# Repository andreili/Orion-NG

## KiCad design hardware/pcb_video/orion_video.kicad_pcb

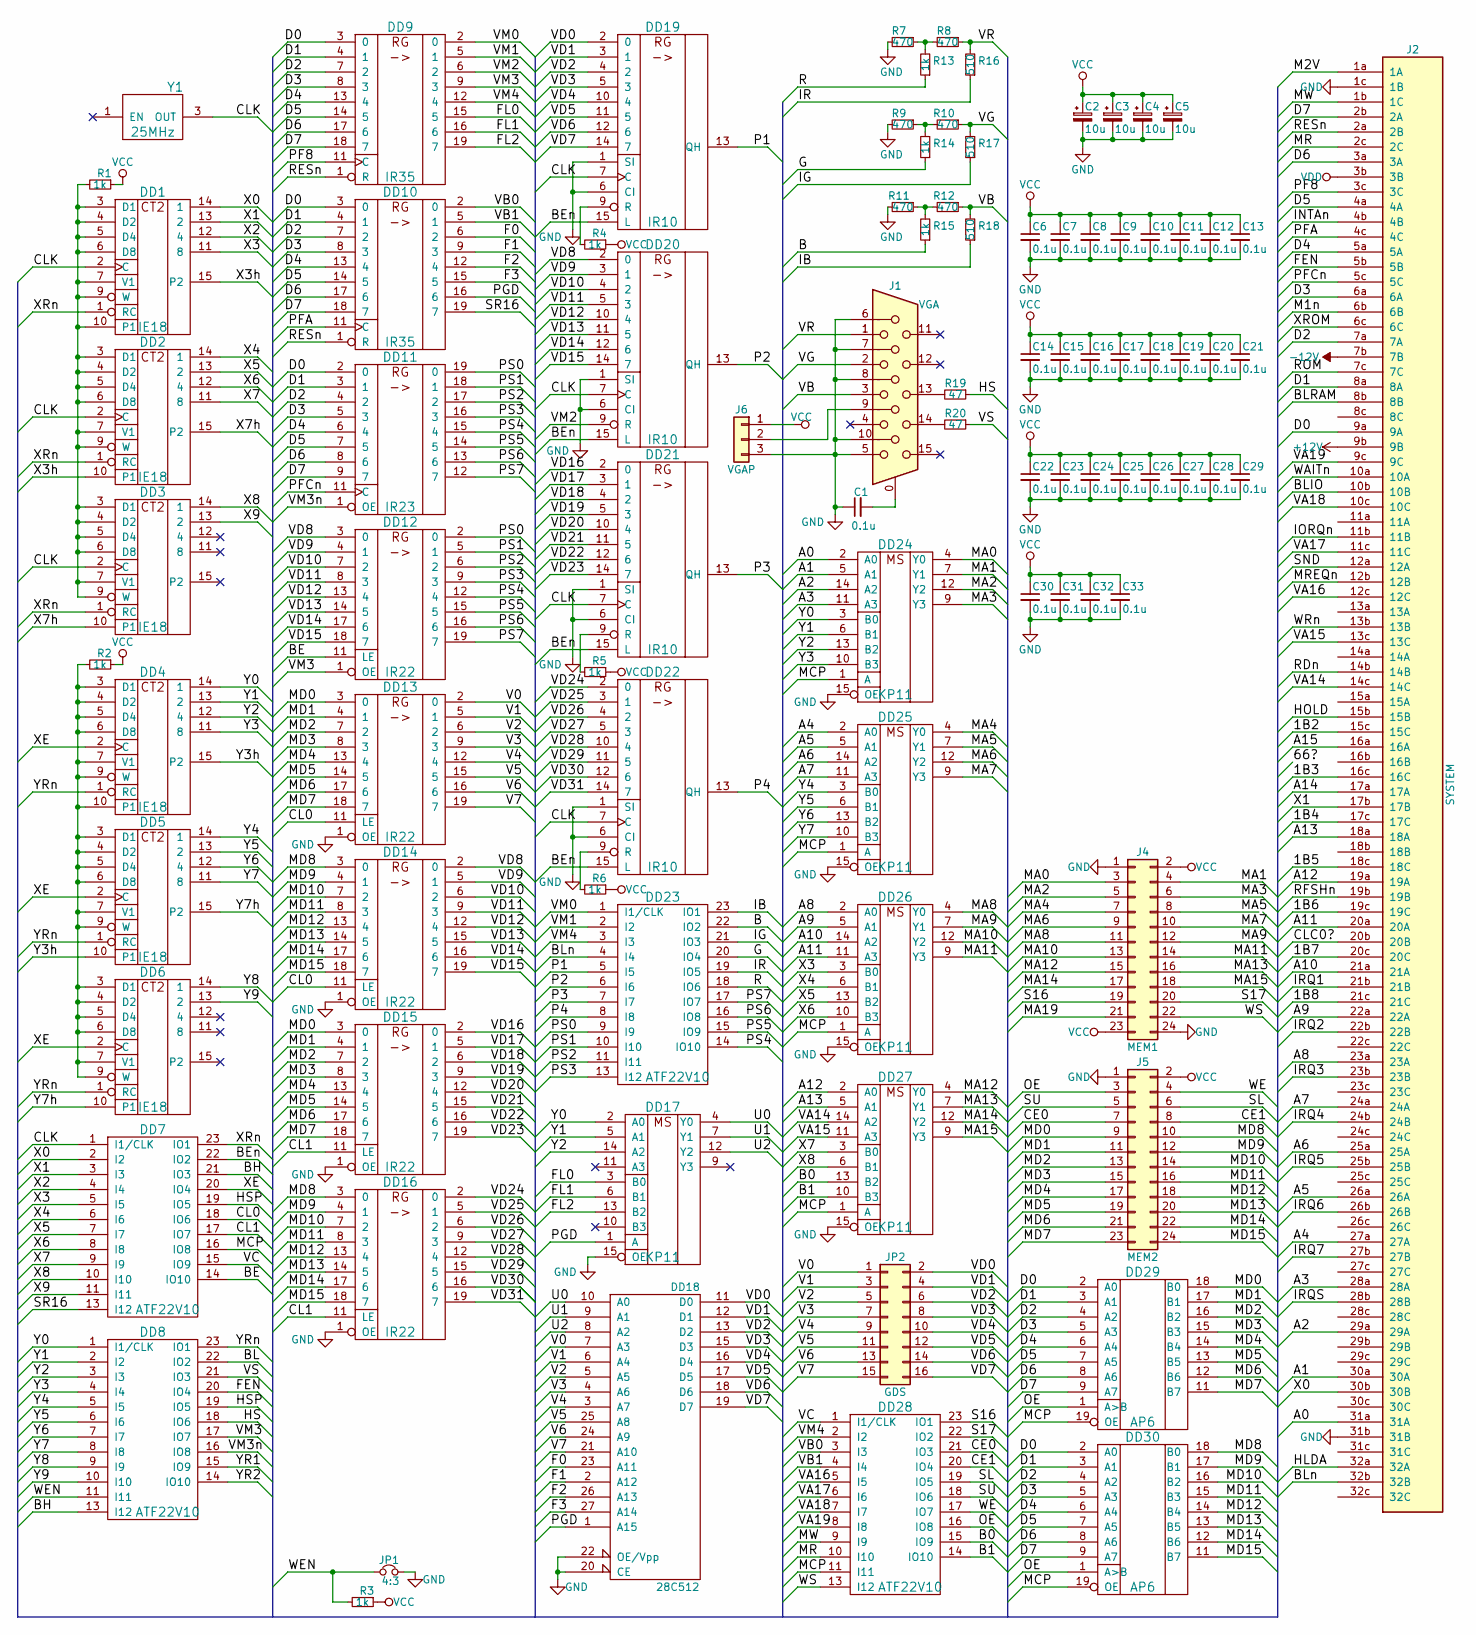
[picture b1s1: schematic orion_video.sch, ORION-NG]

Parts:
C1, C6, C7, C8, C9, C10, C11, C12, C13, C14, C15, C16, C17, C18, C19, C20, C21, C22, C23, C24, C25, C26, C27, C28, C29, C30, C31, C32, C33: 0.1u; C_0805
C2, C3, C4, C5: 10u; CP_Tantalum_Case-B_EIA-3528-21_Hand
DD1, DD2, DD3, DD4, DD5, DD6: IE18; SOIC-16_3.9x9.9mm_Pitch1.27mm
DD7, DD8, DD23, DD28: ATF22V10; DIP-24_W7.62mm_Socket_LongPads
DD9, DD10: IR35; SOIC-20W_7.5x12.8mm_Pitch1.27mm
DD11: IR23; SOIC-20W_7.5x12.8mm_Pitch1.27mm
DD12, DD13, DD14, DD15, DD16: IR22; SOIC-20W_7.5x12.8mm_Pitch1.27mm
DD17, DD24, DD25, DD26, DD27: KP11; SOIC-16_3.9x9.9mm_Pitch1.27mm
DD18: 28C512; DIP-28_W15.24mm_Socket_LongPads
DD19, DD20, DD21, DD22: IR10; SOIC-16_3.9x9.9mm_Pitch1.27mm
DD29, DD30: AP6; SOIC-20W_7.5x12.8mm_Pitch1.27mm
J1: VGA; DB_15F-VGA
J2: SYSTEM; Socket_DIN41612-CaseC1-full-Male-96Pin-3rows
J4: MEM1; Socket_Strip_Straight_2x12_Pitch2.54mm
J5: MEM2; Socket_Strip_Straight_2x12_Pitch2.54mm
J6: VGAP; Socket_Strip_Straight_1x03_Pitch2.54mm
JP1: 4:3; Socket_Strip_Straight_1x02_Pitch2.54mm
JP2: GDS; Socket_Strip_Straight_2x08_Pitch2.54mm
R1, R2, R3, R4, R5, R6, R13, R14, R15: 1k; R_0805
R7, R8, R9, R10, R11, R12: 470; R_0805
R16, R17, R18: 510; R_0805
R19, R20: 47; R_0805
Y1: 25MHz; Crystal_SMD_7050-4pin_7.0x5.0mm

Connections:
+12V: J2.9b (9B)
-12V: J2.7b (7B)
/1B2: J2.15c (15C)
/1B3: J2.16c (16C)
/1B4: J2.17c (17C)
/1B5: J2.18c (18C)
/1B6: J2.19c (19C)
/1B7: J2.20c (20C)
/1B8: J2.21c (21C)
/A0: DD24.2 (A0), J2.31a (31A)
/A1: DD24.5 (A1), J2.30a (30A)
/A2: DD24.14 (A2), J2.29a (29A)
/A3: DD24.11 (A3), J2.28a (28A)
/A4: DD25.2 (A0), J2.27a (27A)
/A5: DD25.5 (A1), J2.26a (26A)
/A6: DD25.14 (A2), J2.25a (25A)
/A7: DD25.11 (A3), J2.24a (24A)
/A8: DD26.2 (A0), J2.23a (23A)
/A9: DD26.5 (A1), J2.22a (22A)
/A10: DD26.14 (A2), J2.21a (21A)
/A11: DD26.11 (A3), J2.20a (20A)
/A12: DD27.2 (A0), J2.19a (19A)
/A13: DD27.5 (A1), J2.18a (18A)
/A14: J2.17a (17A)
/A15: J2.16a (16A)
/B: DD23.22 (IO2), R15.1
/B0: DD27.13 (B2), DD28.15 (IO9)
/B1: DD27.10 (B3), DD28.14 (IO10)
/BE: DD7.14 (IO10), DD12.11 (LE)
/BEn: DD7.22 (IO2), DD19.15 (L), DD20.15 (L), DD21.15 (L), DD22.15 (L)
/BH: DD7.21 (IO3), DD8.13 (I12)
/BL: DD8.22 (IO2)
/BLIO: J2.10b (10B)
/BLRAM: J2.8b (8B)
/BLn: DD23.4 (I4), J2.32b (32B)
/CE0: DD28.21 (IO3), J5.7
/CE1: DD28.20 (IO4), J5.8
/CL0: DD7.18 (IO6), DD13.11 (LE), DD14.11 (LE)
/CL1: DD7.17 (IO7), DD15.11 (LE), DD16.11 (LE)
/CLC0?: J2.20b (20B)
/CLK: DD1.2 (C), DD2.2 (C), DD3.2 (C), DD7.1 (I1/CLK), DD19.7 (C), DD20.7 (C), DD21.7 (C), DD22.7 (C), Y1.3 (OUT)
/D0: DD9.3 (0), DD10.3 (0), DD11.2 (0), DD29.2 (A0), DD30.2 (A0), J2.9a (9A)
/D1: DD9.4 (1), DD10.4 (1), DD11.3 (1), DD29.3 (A1), DD30.3 (A1), J2.8a (8A)
/D2: DD9.7 (2), DD10.7 (2), DD11.4 (2), DD29.4 (A2), DD30.4 (A2), J2.7a (7A)
/D3: DD9.8 (3), DD10.8 (3), DD11.5 (3), DD29.5 (A3), DD30.5 (A3), J2.6a (6A)
/D4: DD9.13 (4), DD10.13 (4), DD11.6 (4), DD29.6 (A4), DD30.6 (A4), J2.5a (5A)
/D5: DD9.14 (5), DD10.14 (5), DD11.7 (5), DD29.7 (A5), DD30.7 (A5), J2.4a (4A)
/D6: DD9.17 (6), DD10.17 (6), DD11.8 (6), DD29.8 (A6), DD30.8 (A6), J2.3a (3A)
/D7: DD9.18 (7), DD10.18 (7), DD11.9 (7), DD29.9 (A7), DD30.9 (A7), J2.2b (2A)
/F0: DD10.6 (2), DD18.23 (A11)
/F1: DD10.9 (3), DD18.2 (A12)
/F2: DD10.12 (4), DD18.26 (A13)
/F3: DD10.15 (5), DD18.27 (A14)
/FEN: DD8.20 (IO4), J2.5b (5B)
/FL0: DD9.15 (5), DD17.3 (B0)
/FL1: DD9.16 (6), DD17.6 (B1)
/FL2: DD9.19 (7), DD17.13 (B2)
/G: DD23.20 (IO4), R14.1
/HLDA: J2.32a (32A)
/HOLD: J2.15b (15B)
/HS: DD8.18 (IO6), R19.1
/HSP: DD7.19 (IO5), DD8.19 (IO5)
/IB: DD23.23 (IO1), R18.1
/IG: DD23.21 (IO3), R17.1
/INTAn: J2.4b (4B)
/IORQn: J2.11b (11B)
/IR: DD23.19 (IO5), R16.1
/IRQ1: J2.21b (21B)
/IRQ2: J2.22b (22B)
/IRQ3: J2.23b (23B)
/IRQ4: J2.24b (24B)
/IRQ5: J2.25b (25B)
/IRQ6: J2.26b (26B)
/IRQ7: J2.27b (27B)
/IRQS: J2.28b (28B)
/M1n: J2.6b (6B)
/M2V: J2.1a (1A)
/MA0: DD24.4 (Y0), J4.3
/MA1: DD24.7 (Y1), J4.4
/MA2: DD24.12 (Y2), J4.5
/MA3: DD24.9 (Y3), J4.6
/MA4: DD25.4 (Y0), J4.7
/MA5: DD25.7 (Y1), J4.8
/MA6: DD25.12 (Y2), J4.9
/MA7: DD25.9 (Y3), J4.10
/MA8: DD26.4 (Y0), J4.11
/MA9: DD26.7 (Y1), J4.12
/MA10: DD26.12 (Y2), J4.13
/MA11: DD26.9 (Y3), J4.14
/MA12: DD27.4 (Y0), J4.15
/MA13: DD27.7 (Y1), J4.16
/MA14: DD27.12 (Y2), J4.17
/MA15: DD27.9 (Y3), J4.18
/MA19: J4.21
/MCP: DD7.16 (IO8), DD24.1 (A), DD25.1 (A), DD26.1 (A), DD27.1 (A), DD28.11 (I11), DD29.19 (OE), DD30.19 (OE)
/MD0: DD13.3 (0), DD15.3 (0), DD29.18 (B0), J5.9
/MD1: DD13.4 (1), DD15.4 (1), DD29.17 (B1), J5.11
/MD2: DD13.7 (2), DD15.7 (2), DD29.16 (B2), J5.13
/MD3: DD13.8 (3), DD15.8 (3), DD29.15 (B3), J5.15
/MD4: DD13.13 (4), DD15.13 (4), DD29.14 (B4), J5.17
/MD5: DD13.14 (5), DD15.14 (5), DD29.13 (B5), J5.19
/MD6: DD13.17 (6), DD15.17 (6), DD29.12 (B6), J5.21
/MD7: DD13.18 (7), DD15.18 (7), DD29.11 (B7), J5.23
/MD8: DD14.3 (0), DD16.3 (0), DD30.18 (B0), J5.10
/MD9: DD14.4 (1), DD16.4 (1), DD30.17 (B1), J5.12
/MD10: DD14.7 (2), DD16.7 (2), DD30.16 (B2), J5.14
/MD11: DD14.8 (3), DD16.8 (3), DD30.15 (B3), J5.16
/MD12: DD14.13 (4), DD16.13 (4), DD30.14 (B4), J5.18
/MD13: DD14.14 (5), DD16.14 (5), DD30.13 (B5), J5.20
/MD14: DD14.17 (6), DD16.17 (6), DD30.12 (B6), J5.22
/MD15: DD14.18 (7), DD16.18 (7), DD30.11 (B7), J5.24
/MR: DD28.10 (I10), J2.2c (2C)
/MREQn: J2.12b (12B)
/MW: DD28.9 (I9), J2.1b (1C)
/OE: DD28.16 (IO8), DD29.1 (A>B), DD30.1 (A>B), J5.3
/P1: DD19.13 (QH), DD23.5 (I5)
/P2: DD20.13 (QH), DD23.6 (I6)
/P3: DD21.13 (QH), DD23.7 (I7)
/P4: DD22.13 (QH), DD23.8 (I8)
/PF8: DD9.11 (C), J2.3c (3C)
/PFA: DD10.11 (C), J2.4c (4C)
/PFCn: DD11.11 (C), J2.5c (5C)
/PGD: DD10.16 (6), DD17.1 (A), DD18.1 (A15)
/PS0: DD11.19 (0), DD12.2 (0), DD23.9 (I9)
/PS1: DD11.18 (1), DD12.5 (1), DD23.10 (I10)
/PS2: DD11.17 (2), DD12.6 (2), DD23.11 (I11)
/PS3: DD11.16 (3), DD12.9 (3), DD23.13 (I12)
/PS4: DD11.15 (4), DD12.12 (4), DD23.14 (IO10)
/PS5: DD11.14 (5), DD12.15 (5), DD23.15 (IO9)
/PS6: DD11.13 (6), DD12.16 (6), DD23.16 (IO8)
/PS7: DD11.12 (7), DD12.19 (7), DD23.17 (IO7)
/R: DD23.18 (IO6), R13.1
/RDn: J2.14b (14B)
/RESn: DD9.1 (R), DD10.1 (R), J2.2a (2B)
/RFSHn: J2.19b (19B)
/ROM: J2.7c (7C)
/S16: DD28.23 (IO1), J4.19
/S17: DD28.22 (IO2), J4.20
/SL: DD28.19 (IO5), J5.6
/SND: J2.12a (12A)
/SR16: DD7.13 (I12), DD10.19 (7)
/SU: DD28.18 (IO6), J5.5
/U0: DD17.4 (Y0), DD18.10 (A0)
/U1: DD17.7 (Y1), DD18.9 (A1)
/U2: DD17.12 (Y2), DD18.8 (A2)
/V0: DD13.2 (0), DD18.7 (A3), JP2.1
/V1: DD13.5 (1), DD18.6 (A4), JP2.3
/V2: DD13.6 (2), DD18.5 (A5), JP2.5
/V3: DD13.9 (3), DD18.4 (A6), JP2.7
/V4: DD13.12 (4), DD18.3 (A7), JP2.9
/V5: DD13.15 (5), DD18.25 (A8), JP2.11
/V6: DD13.16 (6), DD18.24 (A9), JP2.13
/V7: DD13.19 (7), DD18.21 (A10), JP2.15
/VA14: DD27.14 (A2), J2.14c (14C)
/VA15: DD27.11 (A3), J2.13c (13C)
/VA16: DD28.5 (I5), J2.12c (12C)
/VA17: DD28.6 (I6), J2.11c (11C)
/VA18: DD28.7 (I7), J2.10c (10C)
/VA19: DD28.8 (I8), J2.9c (9C)
/VB: J1.3, R12.1, R18.2
/VB0: DD10.2 (0), DD28.3 (I3)
/VB1: DD10.5 (1), DD28.4 (I4)
/VC: DD7.15 (IO9), DD28.1 (I1/CLK)
/VD0: DD18.11 (D0), DD19.2 (0), JP2.2
/VD1: DD18.12 (D1), DD19.3 (1), JP2.4
/VD2: DD18.13 (D2), DD19.4 (2), JP2.6
/VD3: DD18.15 (D3), DD19.5 (3), JP2.8
/VD4: DD18.16 (D4), DD19.10 (4), JP2.10
/VD5: DD18.17 (D5), DD19.11 (5), JP2.12
/VD6: DD18.18 (D6), DD19.12 (6), JP2.14
/VD7: DD18.19 (D7), DD19.14 (7), JP2.16
/VD8: DD12.3 (0), DD14.2 (0), DD20.2 (0)
/VD9: DD12.4 (1), DD14.5 (1), DD20.3 (1)
/VD10: DD12.7 (2), DD14.6 (2), DD20.4 (2)
/VD11: DD12.8 (3), DD14.9 (3), DD20.5 (3)
/VD12: DD12.13 (4), DD14.12 (4), DD20.10 (4)
/VD13: DD12.14 (5), DD14.15 (5), DD20.11 (5)
/VD14: DD12.17 (6), DD14.16 (6), DD20.12 (6)
/VD15: DD12.18 (7), DD14.19 (7), DD20.14 (7)
/VD16: DD15.2 (0), DD21.2 (0)
/VD17: DD15.5 (1), DD21.3 (1)
/VD18: DD15.6 (2), DD21.4 (2)
/VD19: DD15.9 (3), DD21.5 (3)
/VD20: DD15.12 (4), DD21.10 (4)
/VD21: DD15.15 (5), DD21.11 (5)
/VD22: DD15.16 (6), DD21.12 (6)
/VD23: DD15.19 (7), DD21.14 (7)
/VD24: DD16.2 (0), DD22.2 (0)
/VD25: DD16.5 (1), DD22.3 (1)
/VD26: DD16.6 (2), DD22.4 (2)
/VD27: DD16.9 (3), DD22.5 (3)
/VD28: DD16.12 (4), DD22.10 (4)
/VD29: DD16.15 (5), DD22.11 (5)
/VD30: DD16.16 (6), DD22.12 (6)
/VD31: DD16.19 (7), DD22.14 (7)
/VG: J1.2, R10.1, R17.2
/VM0: DD9.2 (0), DD23.1 (I1/CLK)
/VM1: DD9.5 (1), DD23.2 (I2)
/VM2: DD9.6 (2), DD20.9 (R)
/VM3: DD8.17 (IO7), DD9.9 (3), DD12.1 (OE)
/VM3n: DD8.16 (IO8), DD11.1 (OE)
/VM4: DD9.12 (4), DD23.3 (I3), DD28.2 (I2)
/VR: J1.1, R8.1, R16.2
/VS: DD8.21 (IO3), R20.1
/WAITn: J2.10a (10A)
/WE: DD28.17 (IO7), J5.4
/WEN: DD8.11 (I11), JP1.1, R3.2
/WRn: J2.13b (13B)
/WS: DD28.13 (I12), J4.22
/X0: DD1.14 (1), DD7.2 (I2), J2.30b (30B)
/X1: DD1.13 (2), DD7.3 (I3), J2.17b (17B)
/X2: DD1.12 (4), DD7.4 (I4)
/X3: DD1.11 (8), DD7.5 (I5), DD26.3 (B0)
/X3h: DD1.15 (P2), DD2.10 (P1)
/X4: DD2.14 (1), DD7.6 (I6), DD26.6 (B1)
/X5: DD2.13 (2), DD7.7 (I7), DD26.13 (B2)
/X6: DD2.12 (4), DD7.8 (I8), DD26.10 (B3)
/X7: DD2.11 (8), DD7.9 (I9), DD27.3 (B0)
/X7h: DD2.15 (P2), DD3.10 (P1)
/X8: DD3.14 (1), DD7.10 (I10), DD27.6 (B1)
/X9: DD3.13 (2), DD7.11 (I11)
/XE: DD4.2 (C), DD5.2 (C), DD6.2 (C), DD7.20 (IO4)
/XROM: J2.6c (6C)
/XRn: DD1.1 (RC), DD2.1 (RC), DD3.1 (RC), DD7.23 (IO1)
/Y0: DD4.14 (1), DD8.1 (I1/CLK), DD17.2 (A0), DD24.3 (B0)
/Y1: DD4.13 (2), DD8.2 (I2), DD17.5 (A1), DD24.6 (B1)
/Y2: DD4.12 (4), DD8.3 (I3), DD17.14 (A2), DD24.13 (B2)
/Y3: DD4.11 (8), DD8.4 (I4), DD24.10 (B3)
/Y3h: DD4.15 (P2), DD5.10 (P1)
/Y4: DD5.14 (1), DD8.5 (I5), DD25.3 (B0)
/Y5: DD5.13 (2), DD8.6 (I6), DD25.6 (B1)
/Y6: DD5.12 (4), DD8.7 (I7), DD25.13 (B2)
/Y7: DD5.11 (8), DD8.8 (I8), DD25.10 (B3)
/Y7h: DD5.15 (P2), DD6.10 (P1)
/Y8: DD6.14 (1), DD8.9 (I9)
/Y9: DD6.13 (2), DD8.10 (I10)
/YR1: DD8.15 (IO9)
/YR2: DD8.14 (IO10)
/YRn: DD4.1 (RC), DD5.1 (RC), DD6.1 (RC), DD8.23 (IO1)
GND: C1.1, C2.2, C3.2, C4.2, C5.2, C6.2, C7.2, C8.2, C9.2, C10.2, C11.2, C12.2, C13.2, C14.2, C15.2, C16.2, C17.2, C18.2, C19.2, C20.2, C21.2, C22.2, C23.2, C24.2, C25.2, C26.2, C27.2, C28.2, C29.2, C30.2, C31.2, C32.2, C33.2, DD1.8 (GND), DD2.8 (GND), DD3.8 (GND), DD4.8 (GND), DD5.8 (GND), DD6.8 (GND), DD7.12 (GND), DD8.12 (GND), DD9.10 (GND), DD10.10 (GND), DD11.10 (GND), DD12.10 (GND), DD13.1 (OE), DD13.10 (GND), DD14.1 (OE), DD14.10 (GND), DD15.1 (OE), DD15.10 (GND), DD16.1 (OE), DD16.10 (GND), DD17.8 (GND), DD17.15 (OE), DD18.14 (GND), DD18.20 (CE), DD18.22 (OE/Vpp), DD19.1 (SI), DD19.6 (CI), DD19.8 (GND), DD20.1 (SI), DD20.6 (CI), DD20.8 (GND), DD21.1 (SI), DD21.6 (CI), DD21.8 (GND), DD22.1 (SI), DD22.6 (CI), DD22.8 (GND), DD23.12 (GND), DD24.8 (GND), DD24.15 (OE), DD25.8 (GND), DD25.15 (OE), DD26.8 (GND), DD26.15 (OE), DD27.8 (GND), DD27.15 (OE), DD28.12 (GND), DD29.10 (GND), DD30.10 (GND), J1.5, J1.6, J1.7, J1.8, J1.10, J2.1c (1B), J2.31b (31B), J4.1, J4.24, J5.1, J6.3, JP1.2, R7.2, R9.2, R11.2, Y1.2 (GND)
unnamed: C1.2, J1.0
unnamed: DD1.3 (D1), DD1.4 (D2), DD1.5 (D4), DD1.6 (D8), DD1.7 (V1), DD1.9 (W), DD1.10 (P1), DD2.3 (D1), DD2.4 (D2), DD2.5 (D4), DD2.6 (D8), DD2.7 (V1), DD2.9 (W), DD3.3 (D1), DD3.4 (D2), DD3.5 (D4), DD3.6 (D8), DD3.7 (V1), DD3.9 (W), R1.2
unnamed: DD4.3 (D1), DD4.4 (D2), DD4.5 (D4), DD4.6 (D8), DD4.7 (V1), DD4.9 (W), DD4.10 (P1), DD5.3 (D1), DD5.4 (D2), DD5.5 (D4), DD5.6 (D8), DD5.7 (V1), DD5.9 (W), DD6.3 (D1), DD6.4 (D2), DD6.5 (D4), DD6.6 (D8), DD6.7 (V1), DD6.9 (W), R2.2
unnamed: DD19.9 (R), R4.2
unnamed: DD21.9 (R), R5.2
unnamed: DD22.9 (R), R6.2
unnamed: J1.9, J6.2
unnamed: J1.13, R19.2
unnamed: J1.14, R20.2
unnamed: R9.1, R10.2, R14.2
unnamed: R11.1, R12.2, R15.2
unnamed: R7.1, R8.2, R13.2
VCC: C2.1, C3.1, C4.1, C5.1, C6.1, C7.1, C8.1, C9.1, C10.1, C11.1, C12.1, C13.1, C14.1, C15.1, C16.1, C17.1, C18.1, C19.1, C20.1, C21.1, C22.1, C23.1, C24.1, C25.1, C26.1, C27.1, C28.1, C29.1, C30.1, C31.1, C32.1, C33.1, DD1.16 (VCC), DD2.16 (VCC), DD3.16 (VCC), DD4.16 (VCC), DD5.16 (VCC), DD6.16 (VCC), DD7.24 (VCC), DD8.24 (VCC), DD9.20 (VCC), DD10.20 (VCC), DD11.20 (VCC), DD12.20 (VCC), DD13.20 (VCC), DD14.20 (VCC), DD15.20 (VCC), DD16.20 (VCC), DD17.16 (VCC), DD18.28 (VCC), DD19.16 (VCC), DD20.16 (VCC), DD21.16 (VCC), DD22.16 (VCC), DD23.24 (VCC), DD24.16 (VCC), DD25.16 (VCC), DD26.16 (VCC), DD27.16 (VCC), DD28.24 (VCC), DD29.20 (VCC), DD30.20 (VCC), J4.2, J4.23, J5.2, J6.1, R1.1, R2.1, R3.1, R4.1, R5.1, R6.1, Y1.4 (VCC)
VDD: J2.3b (3B)

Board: 2 copper layers, 91 parts (8 on the bottom side), 213 nets, no tracks yet.
